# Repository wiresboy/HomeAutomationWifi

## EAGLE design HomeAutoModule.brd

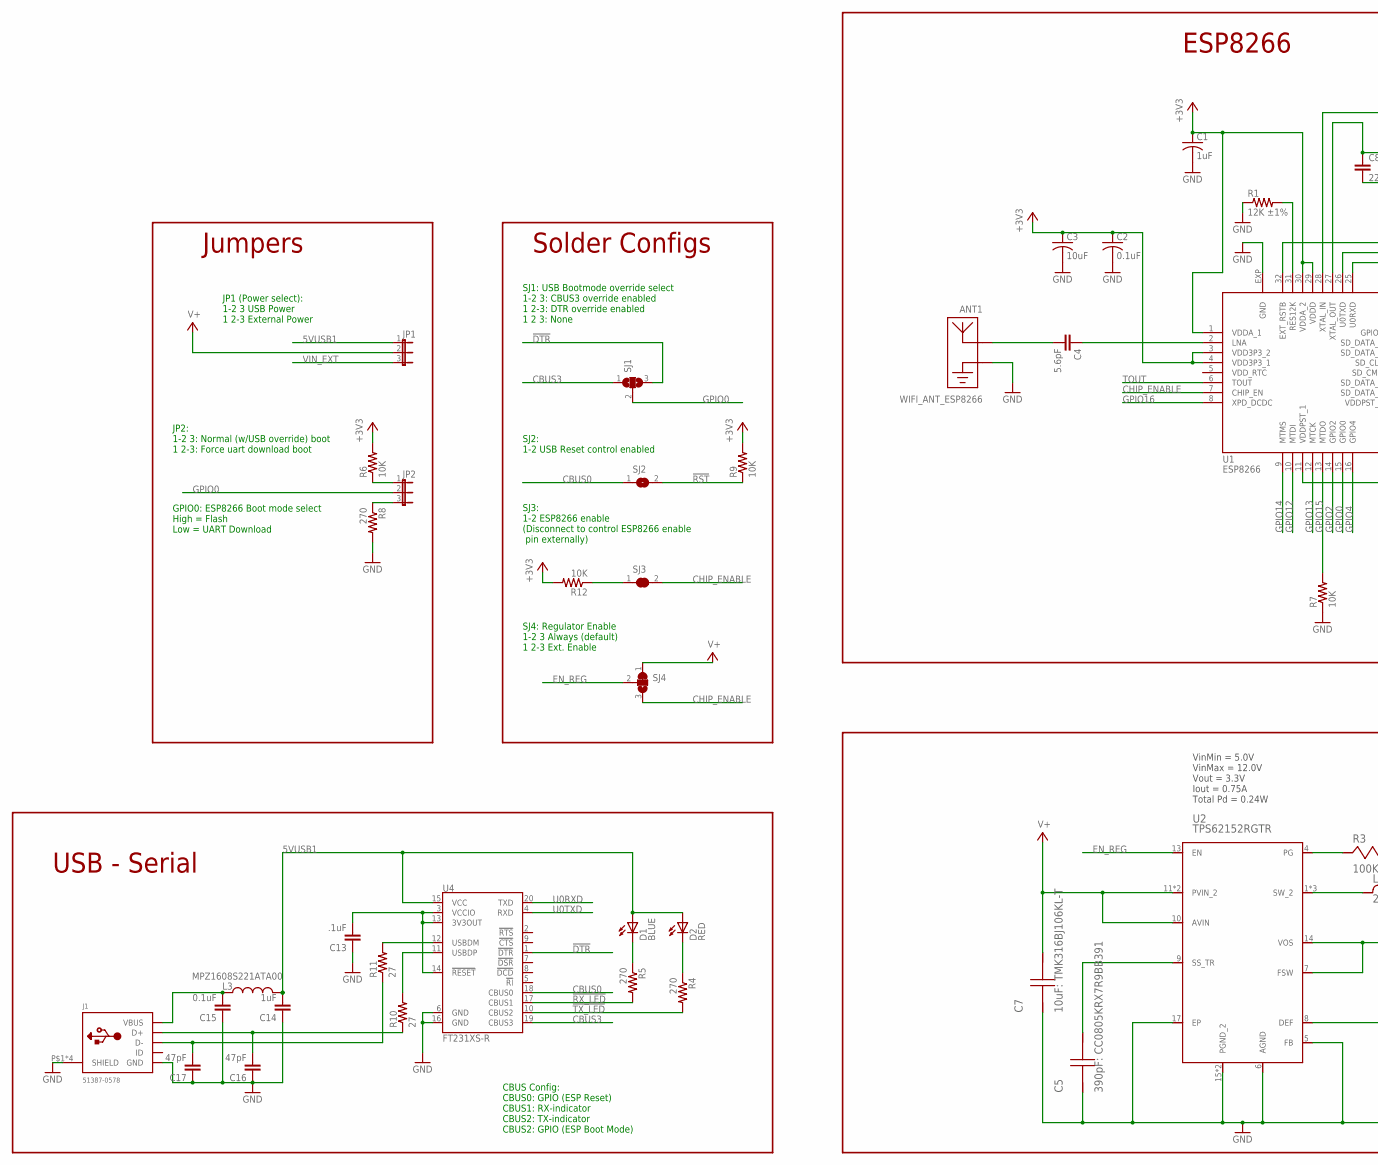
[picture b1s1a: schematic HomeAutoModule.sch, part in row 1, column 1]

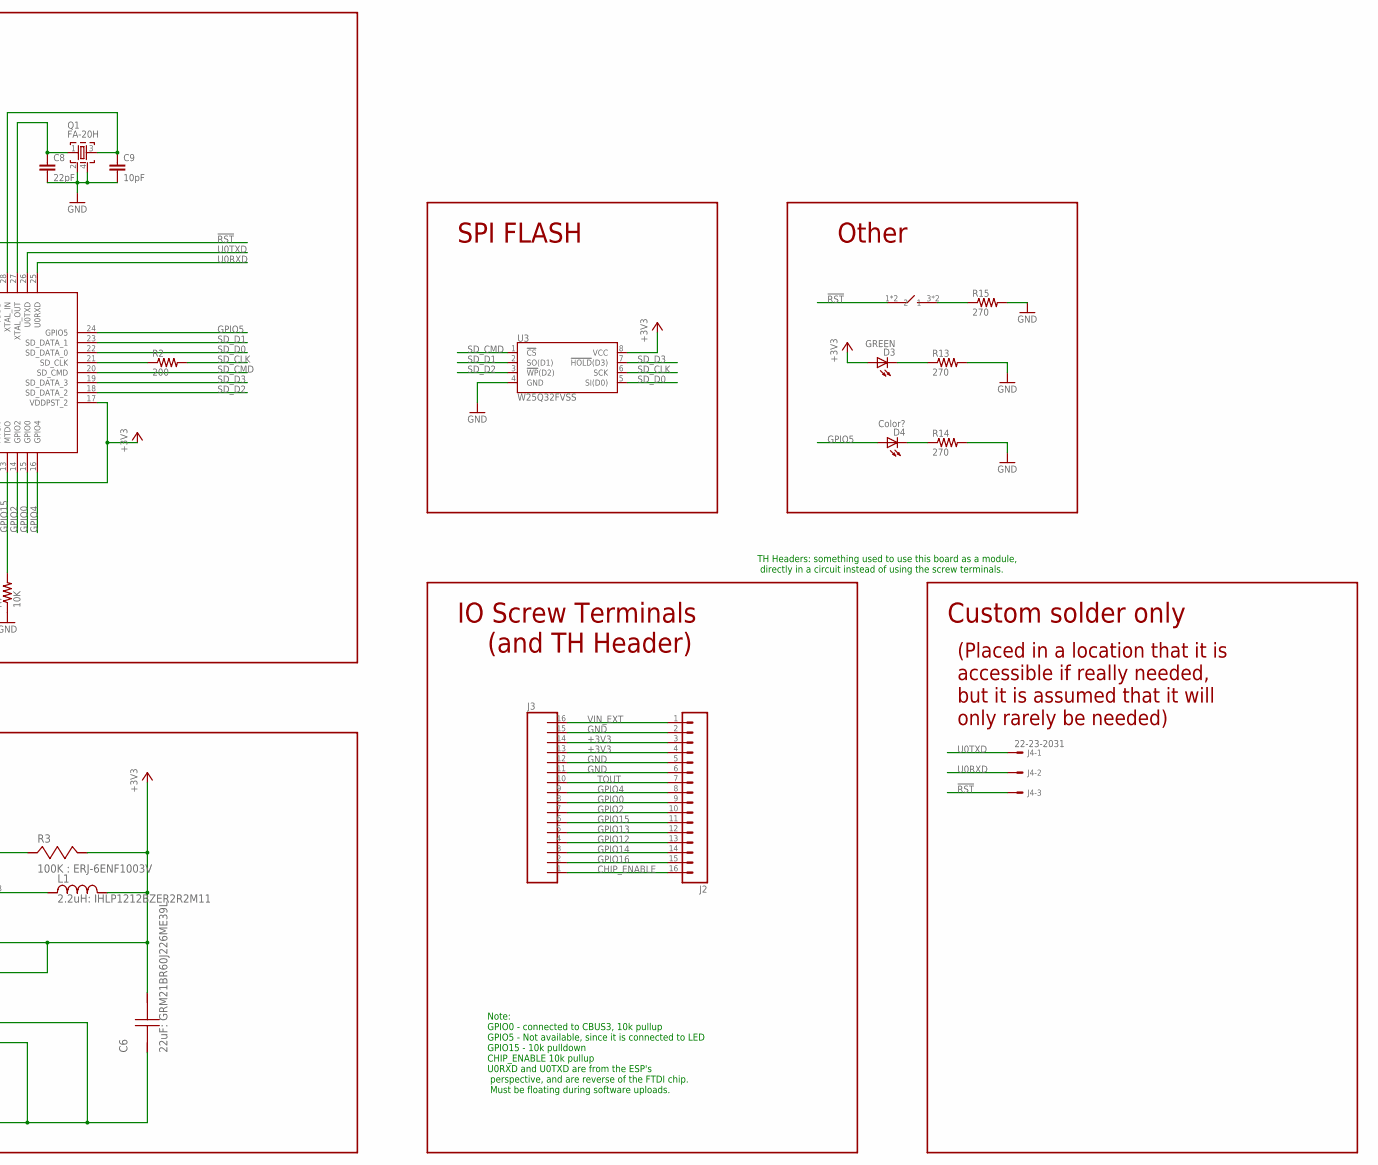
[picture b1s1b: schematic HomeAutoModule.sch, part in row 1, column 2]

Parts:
ANT1: WIFI_ANT_ESP8266; ESP8266_ANT
C1: 1uF; C0603
C2, C15: 0.1uF; C0603K
C3: 10uF; C0805
C4: 5.6pF; C0603
C5: 390pF: CC0805KRX7R9BB391; 0805
C6: 22uF: GRM21BR60J226ME39L; 0805
C7: 10uF: TMK316BJ106KL-T; 1206
C8: 22pF; C0603
C9: 10pF; C0603
C13: .1uF; C0603K
C14: 1uF; C0603K
C16, C17: 47pF; C0603K
D1: BLUE; CHIPLED_0603
D2: RED; CHIPLED_0603
D3: GREEN; CHIPLED_0603
D4: Color?; CHIPLED_0603
J1: 51387-0578; USB-MINIB-0513870578
J2: M161X16_NO_SILK; 1X16_NO_SILK
J3: PTSA_250_16; PTSA_250_16_F
J4: 22-23-2031
JP1, JP2: JP2E; JP2
L1: 2.2uH: IHLP1212BZER2R2M11; IHLP-1212BZ
L3: MPZ1608S221ATA00; 0603
Q1: FA-20H
R1: 12K ±1%; R0603
R2: 200; R0603
R3: 100K : ERJ-6ENF1003V; 0805
R4, R5, R8, R13, R14, R15: 270; R0603
R6, R7, R9, R12: 10K; R0603
R10, R11: 27; R0603
SJ1: SJ2W; SJ_2
SJ2: SJ
SJ3: SJ_C
SJ4: SJ2_C; SJ_2_C
SW1: PTS645SM43SMTR92DEFAULT; PTS645SM43SMTR92
U1: ESP8266; HVQFN32
U2: TPS62152RGTR; S-PVQFN-N16
U3: W25Q32FVSS; SOIC-8
U4: FT231XS-R; SSOP20_L

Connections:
5VUSB1: C14.2, D1.A, D2.A, JP1.1, L3.2, U4.15 (VCC)
!DTR: SJ1.3, U4.1 (!DTR)
!RST: J4.3, R9.1, SJ2.2, SW1.1, SW1.2 (1), U1.32 (EXT_RSTB)
!RX_LED: R5.2, U4.17 (CBUS1)
!TX_LED: R4.2, U4.10 (CBUS2)
+3V3: C1.1, C2.1, C3.1, C6.1, D3.A, J2.3, J2.4, J3.13, J3.14, L1.2, R3.1, R6.2, R9.2, R12.2, U1.1 (VDDA_1), U1.3 (VDD3P3_2), U1.4 (VDD3P3_1), U1.11 (VDDPST_1), U1.17 (VDDPST_2), U1.29 (VDDD), U1.30 (VDDA_2), U2.7 (FSW), U2.14 (VOS), U3.8 (VCC)
CBUS0: SJ2.1, U4.18 (CBUS0)
CBUS3: SJ1.1, U4.19 (CBUS3)
CHIP_ENABLE: J2.16, J3.1, SJ3.2, SJ4.3, U1.7 (CHIP_EN)
EN_REG: SJ4.2, U2.13 (EN)
ESP_12K: R1.2, U1.31 (RES12K)
GND: ANT1.GND, C1.2, C2.2, C3.2, C5.2, C6.2, C7.2, C8.2, C9.2, C13.1, C14.1, C15.1, C16.1, C17.1, J1.GND, J1.P$1 (SHIELD), J1.P$2 (SHIELD), J1.P$3 (SHIELD), J1.P$4 (SHIELD), J2.2, J2.5, J2.6, J3.11, J3.12, J3.15, Q1.2, Q1.4, R1.1, R7.1, R8.2, R13.2, R14.2, R15.2, U1.EXP (GND), U2.5 (FB), U2.6 (AGND), U2.8 (DEF), U2.15 (PGND_2), U2.16 (PGND_2), U2.17 (EP), U3.4 (GND), U4.6 (GND), U4.16 (GND)
GPIO0: J2.9, J3.8, JP2.2, SJ1.2, U1.15 (GPIO0)
GPIO2: J2.10, J3.7, U1.14 (GPIO2)
GPIO4: J2.8, J3.9, U1.16 (GPIO4)
GPIO5: D4.A, U1.24 (GPIO5)
GPIO12: J2.13, J3.4, U1.10 (MTDI)
GPIO13: J2.12, J3.5, U1.12 (MTCK)
GPIO14: J2.14, J3.3, U1.9 (MTMS)
GPIO15: J2.11, J3.6, R7.2, U1.13 (MTDO)
GPIO16: J2.15, J3.2, U1.8 (XPD_DCDC)
LNA: C4.1, U1.2 (LNA)
unnamed: R2.1, U1.21 (SD_CLK)
unnamed: ANT1.ANT, C4.2
unnamed: JP2.3, R8.1
unnamed: C5.1, U2.9 (SS_TR)
unnamed: JP2.1, R6.1
unnamed: R3.2, U2.4 (PG)
unnamed: L1.1, U2.1 (SW_2), U2.2 (SW_2), U2.3 (SW_2)
unnamed: C13.2, U4.3 (VCCIO), U4.13 (3V3OUT), U4.14 (!RESET)
unnamed: D2.C, R4.1
unnamed: D1.C, R5.1
unnamed: R11.2, U4.12 (USBDM)
unnamed: R12.1, SJ3.1
unnamed: R10.2, U4.11 (USBDP)
unnamed: D3.C, R13.1
unnamed: D4.C, R14.1
unnamed: R15.1, SW1.3 (2), SW1.4 (2)
SD_CLK: R2.2, U3.6 (SCK)
SD_CMD: U1.20 (SD_CMD), U3.1 (!CS!)
SD_D0: U1.22 (SD_DATA_0), U3.5 (SI(D0))
SD_D1: U1.23 (SD_DATA_1), U3.2 (SO(D1))
SD_D2: U1.18 (SD_DATA_2), U3.3 (!WP!(D2))
SD_D3: U1.19 (SD_DATA_3), U3.7 (!HOLD!(D3))
TOUT: J2.7, J3.10, U1.6 (TOUT)
U0RXD: J4.2, U1.25 (U0RXD), U4.20 (TXD)
U0TXD: J4.1, U1.26 (U0TXD), U4.4 (RXD)
USB_D+: C16.2, J1.D+, R10.1
USB_D-: C17.2, J1.D-, R11.1
USB_VBUS: C15.2, J1.VBUS, L3.1
V+: C7.1, JP1.2, SJ4.1, U2.10 (AVIN), U2.11 (PVIN_2), U2.12 (PVIN_2)
VIN_EXT: J2.1, J3.16, JP1.3
XTAL_IN: C9.1, Q1.3, U1.28 (XTAL_IN)
XTAL_OUT: C8.1, Q1.1, U1.27 (XTAL_OUT)

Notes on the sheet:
VinMin = 5.0V VinMax = 12.0V Vout = 3.3V Iout = 0.75A Total Pd = 0.24W
CBUS Config: CBUS0: GPIO (ESP Reset) CBUS1: RX-indicator CBUS2: TX-indicator CBUS2: GPIO (ESP Boot Mode)
GPIO0: ESP8266 Boot mode select High = Flash Low = UART Download
JP2: 1-2 3: Normal (w/USB override) boot 1 2-3: Force uart download boot
SJ1: USB Bootmode override select 1-2 3: CBUS3 override enabled 1 2-3: DTR override enabled 1 2 3: None
SJ2: 1-2 USB Reset control enabled
SJ3: 1-2 ESP8266 enable (Disconnect to control ESP8266 enable pin externally)
Solder Configs
JP1 (Power select): 1-2 3 USB Power 1 2-3 External Power
Jumpers
IO Screw Terminals
Note: GPIO0 - connected to CBUS3, 10k pullup GPIO5 - Not available, since it is connected to LED GPIO15 - 10k pulldown CHIP_ENABLE 10k pullup U0RXD and U0TXD are from the ESP's perspective, and are reverse of the FTDI chip. Must be floating during software uploads.
SJ4: Regulator Enable 1-2 3 Always (default) 1 2-3 Ext. Enable
Custom solder only
SPI FLASH
ESP8266
USB - Serial
Other
(and TH Header)
TH Headers: something used to use this board as a module, directly in a circuit instead of using the screw terminals.
(Placed in a location that it is accessible if really needed, but it is assumed that it will only rarely be needed)

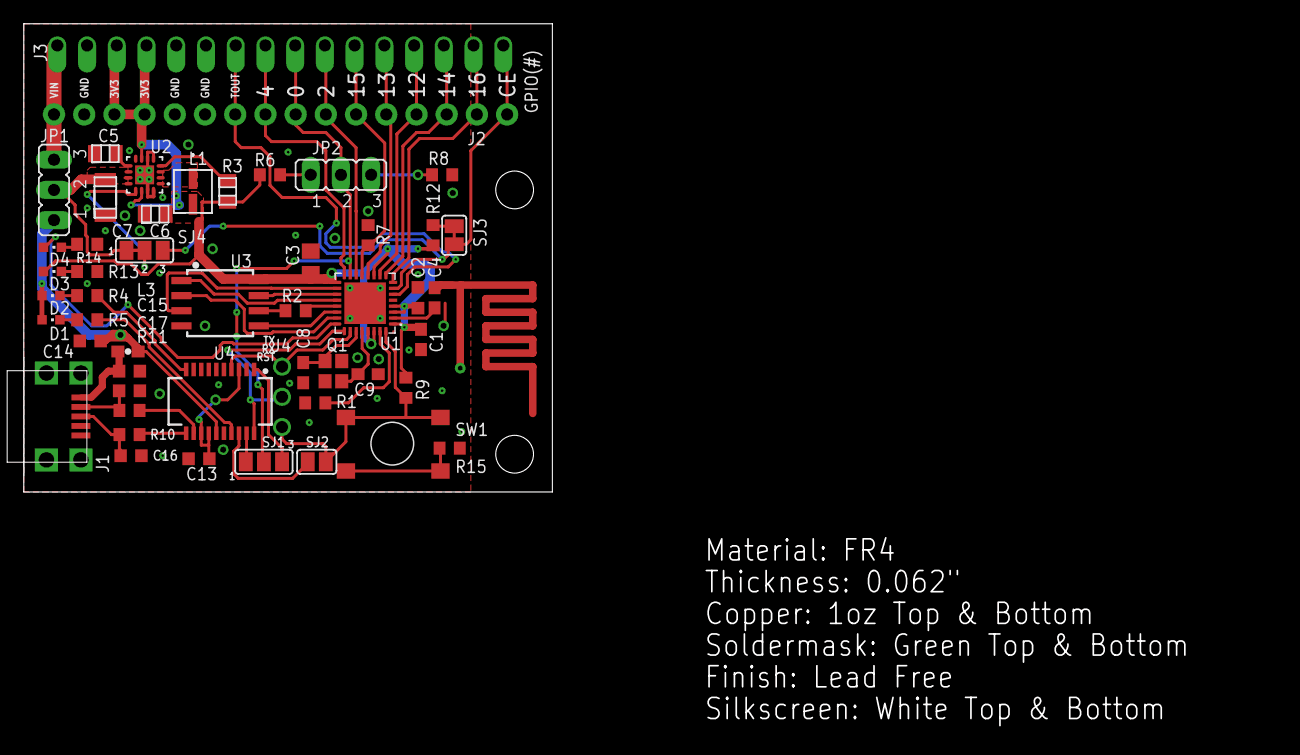
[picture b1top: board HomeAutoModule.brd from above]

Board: 2 copper layers, 44.5 x 39.4 mm, 53 parts (0 on the bottom side), 54 nets.

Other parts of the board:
DRILEGEND: DRILEGEND

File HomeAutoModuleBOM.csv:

"Qty","Value","Device","Package","Parts","Description",""
"2","","JP2E","JP2","JP1, JP2","JUMPER",""
"1","","M161X16_NO_SILK","1X16_NO_SILK","J2","1x16 .1" header",""
"1","","SJ","SJ","SJ2","SMD solder JUMPER",""
"1","","SJ2W","SJ_2","SJ1","SMD solder JUMPER",""
"1","","SJ2_C","SJ_2_C","SJ4","SMD solder JUMPER",""
"1","","SJ_C","SJ_C","SJ3","SMD solder JUMPER",""
"1",".1uF","C-EUC0603K","C0603K","C13","CAPACITOR, European symbol",""
"1","0.1uF","C-EUC0603K","C0603K","C15","CAPACITOR, European symbol",""
"1","0.1uF","C-USC0603K","C0603K","C2","CAPACITOR, American symbol",""
"1","100K : ERJ-6ENF1003V","ERJ-6ENF1003V","0805","R3","",""
"4","10K","R-US_R0603","R0603","R6, R7, R9, R12","RESISTOR, American symbol",""
"1","10pF","C-EUC0603","C0603","C9","CAPACITOR, European symbol",""
"1","10uF","C-USC0805","C0805","C3","CAPACITOR, American symbol",""
"1","10uF: TMK316BJ106KL-T","TMK316BJ106KL-T","1206","C7","",""
"1","12K ±1%","R-US_R0603","R0603","R1","RESISTOR, American symbol",""
"1","1uF","C-EUC0603K","C0603K","C14","CAPACITOR, European symbol",""
"1","1uF","C-USC0603","C0603","C1","CAPACITOR, American symbol",""
"1","2.2uH: IHLP1212BZER2R2M11","IHLP1212BZER2R2M11","IHLP-1212BZ","L1","",""
"1","200","R-US_R0603","R0603","R2","RESISTOR, American symbol",""
"1","22-23-2031","22-23-2031","22-23-2031","J4",".100" (2.54mm) Center Header - 3 Pin",""
"1","22pF","C-EUC0603","C0603","C8","CAPACITOR, European symbol",""
"1","22uF: GRM21BR60J226ME39L","GRM21BR60J226ME39L","0805","C6","",""
"2","27","R-US_R0603","R0603","R10, R11","RESISTOR, American symbol",""
"6","270","R-US_R0603","R0603","R4, R5, R8, R13, R14, R15","RESISTOR, American symbol",""
"1","390pF: CC0805KRX7R9BB391","CC0805KRX7R9BB391","0805","C5","",""
"2","47pF","C-EUC0603K","C0603K","C16, C17","CAPACITOR, European symbol",""
"1","5.6pF","C-EUC0603","C0603","C4","CAPACITOR, European symbol",""
"1","51387-0578","USB","USB-MINIB-0513870578","J1","USB Connectors",""
"1","BLUE","LEDCHIPLED_0603","CHIPLED_0603","D1","LED",""
"1","Color?","LEDCHIPLED_0603","CHIPLED_0603","D4","LED",""
"1","ESP8266","ESP8266","HVQFN32","U1","",""
"1","FA-20H","FA-20H","FA-20H","Q1","MHz RANGE CRYSTAL UNIT",""
"1","FT231XS-R","FT231XS","SSOP20_L","U4","FTDI FT231X Full Speed USB to Full-handshake UART",""
"1","GREEN","LEDCHIPLED_0603","CHIPLED_0603","D3","LED",""
"1","MPZ1608S221ATA00","INDUCTOR0603","0603","L3","Inductors",""
"1","PTS645SM43SMTR92DEFAULT","PTS645SM43SMTR92DEFAULT","PTS645SM43SMTR92","SW1","",""
"1","PTSA_250_16","PTSA_250_16","PTSA_250_16_F","J3","",""
"1","RED","LEDCHIPLED_0603","CHIPLED_0603","D2","LED",""
"1","TPS62152RGTR","TPS62152RGTR","S-PVQFN-N16","U2","",""
"1","W25Q32FVSS","W25Q32FVSS","SOIC-8","U3","Winbond W25Q32FV 32Mbit (4MB) Flash",""
"1","WIFI_ANT_ESP8266","WIFI_ANT_ESP8266","ESP8266_ANT","ANT1","",""

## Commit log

2016-09-30 :octocat: Added .gitattributes & .gitignore files
2016-09-30 Created ESP8266 library
2016-10-02 Found open source antenna library
2016-10-03 Implemented ESP8266 basic layout
2016-10-04 Added TI Power Regulator
    Based on a WEBench design from TI.
2016-10-05 Fixed antenna library
2016-10-14 Added USB, control jumpers
2016-10-14 Prep for IO use
2016-10-15 Added crystal, more USB config
2016-10-15 Refactored schematic for readability
    Also added SPI flash, marked IO to be used at screw terminals
2016-10-15 Added place-holders for "Other" category
    (GPIO LED, reset button)
2016-10-15 Clarified use of UART io lines
2016-10-16 Clarified comments
2016-10-18 Fixed Mr. Emges suggestions, Reset Button
2016-10-18 Renamed Module to HomeAutoBoard
2016-10-21 Started board layout
2016-10-22 Ran traces for flash chip
2016-10-22 USB Routed
2016-10-22 Connected many units
2016-10-22 Rearranged antenna to fit reset button more easily
    It didn't work. May need to find a new button, in which case the antenna
    could be put back.
2016-10-22 reset button routing complete
2016-10-22 Routed power regulator
    3.3v bus still needs routing.
2016-10-23 1st layout pass complete
    Still need all of the connectors, in both schematic and board layout.
    Making sure the core idea in this design is ok, then will proceed.
2016-10-25 Many various tweaks
    All GPIO that I plan on making easily accessible is now routed to the
    edge of the board.
    I am still debating whether I want to keep the UART0_TX/UART0_RX and RST
    lines available, since for the most part they probably wouldn't need to
    be accessed after development, and during the physical button and USB
    could be used.
2016-10-25 Fixed C1 placement for ESP8266
    still may need to adjust C2
2016-10-26 Fixed comments from feedback #3
2016-10-26 Fixed power regulator layout
    per feedback #4
2016-10-26 Better ground via connections
2016-10-26 Made some vias smaller
    Only the ones that were particularly annoying to place, and the via in
    pad ones.
2016-10-26 Dennnis update
    R1, C1, C4, R9 adjusted for better power decoupling cap return paths
2016-10-27 Rerouted GPIO0 to not go under the antenna
    Also made a bunch of the vias smaller, which allowed for cleaner routing
    in many places.
2016-10-27 Organised schematic for future connector connection
2016-10-28 Added connectors to layout, schematic.
2016-10-28 Compacted board layout
2016-10-28 recalculated drc
2016-10-29 Layout out silkscreen layer
2016-10-29 Updated DRU, slight modifications to match it.
2016-10-29 Added hole, pcb annotations
2016-10-29 Generated Gerbers
2016-10-29 Fixed QFN layout for U2
2016-10-31 Gerber update
2016-10-31 Updated 2 more gerbers
2016-10-31 Final gerbers
2016-11-20 Initial FW commit
2016-11-22 Final BOM
2016-11-22 Starting code
2016-11-22 Initial server software
    Based on Captive Intraweb
2016-11-23 Functioning remote control firmware
2016-11-27 More MQTT experiments
    Likely going to scrap MQTT, since a REST server doesn't require extra
    hardware.
2016-11-27 REST server
2016-12-06 The REST HTTP server appears to work!
    These are changes from a while ago that I forgot to commit, IDK what is
    in them. All I know is that it now works.
2016-12-11 Working on auto-boot.
2016-12-11 Fixed some stuff
    It appears that the UPNP service is not compatible with the TrendNet
    router - so this now uses a linksys router.
    Auto-run on boot now works, AP must be connected in the first ~1 minute,
    otherwise a reboot is required.
    Todo: make it so that reboots are not required.

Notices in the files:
parts and their libraries:
SparkFun-Passives: Licensing: Creative Commons ShareAlike 4.0 International - https://creativecommons.org/licenses/by-sa/4.0
